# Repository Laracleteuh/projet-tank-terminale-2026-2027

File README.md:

# projet-tank-terminale-2026-2027 ###

Repo GitHub pour le projet de Tank RC des Terminales spécialités sciences de l'ingénieur. Contenu Open Source, et maintenu jusqu'en juillet 2027

### Configuration Requise ###

Ce projet est basé autour de l'Arduino Mega 2560 programmé via VS Code et son extension PlatformIO.
Sur chaque release un fichier .zip a build et un .hex pouvant être uploadé directement sera disponible.
Le fichier d'environnement platformio.ini est publié dans son dossier /PlatformIO/

### Tank OS ###

La dernière version en date de TankOS est TankOS 1.
[Lien vers la dernière release de TankOS](https://github.com/Laracleteuh/projet-tank-terminale-2026-2027/releases/tag/TOS1.1-FU11102026)

*La documentation technique se trouve dans Manuel Utilisateur / Logiciel / TankOS 1.html - .pdf*

### PCB Custom ###

Ce projet contient quelques cartes électroniques faites sur mesure. Les fichiers de celles-ci seront disponibles plus tard dans l'année, quand leur design sera validé et fonctionnel.
Ces designs ont étés fait sur KiCAD.

### Python Scripts ###

Ce projet contient un dossier réservé à des scripts python. Ils sont fait maison et permettent de calculer des caractéristiques en rapport avec les moteurs plus facilement, n'hesitez pas à vous en servir si besoin ;). Pour moins se casser la tête pour des valeurs par défaut, dans la première input, tapez "def" pour charger les valeurs par défaut du programme. Elles seront mises à jour si jamais elles changent au cours du projet.

### MatLab ###

Ce projet contient un dossier réservé aux modèles MatLab et aux calculs. Dans celui-ci vous pourrez trouver le(s) modèle(s) de simulation des moteurs, et la fiche de calcul qui justifie CHAQUE valeur de MatLab (autre que celle qu'on peut trouver dans les docs techniques, vous pouvez chercher quand même, là c'est que les calculs)

### User Manuals ###

Ce projet contient un dossier réservé aux manuels utilisateurs. Ces manuels seront répartis dans des dossiers selon le type d'élément qu'ils présentent (PCB par exemple)

### Feuilles de Calcul ###

Ce projet contient un dossier réservé aux feuilles de calculs pour le tank. Utile si besoin. (Feuilles manuscrites)

---
### Licence ###

Ce projet est distribué sous licence MIT pour le code. Les schémas électroniques et fichiers PCB sont mis à disposition sous licence CERN-OHL-P v2.

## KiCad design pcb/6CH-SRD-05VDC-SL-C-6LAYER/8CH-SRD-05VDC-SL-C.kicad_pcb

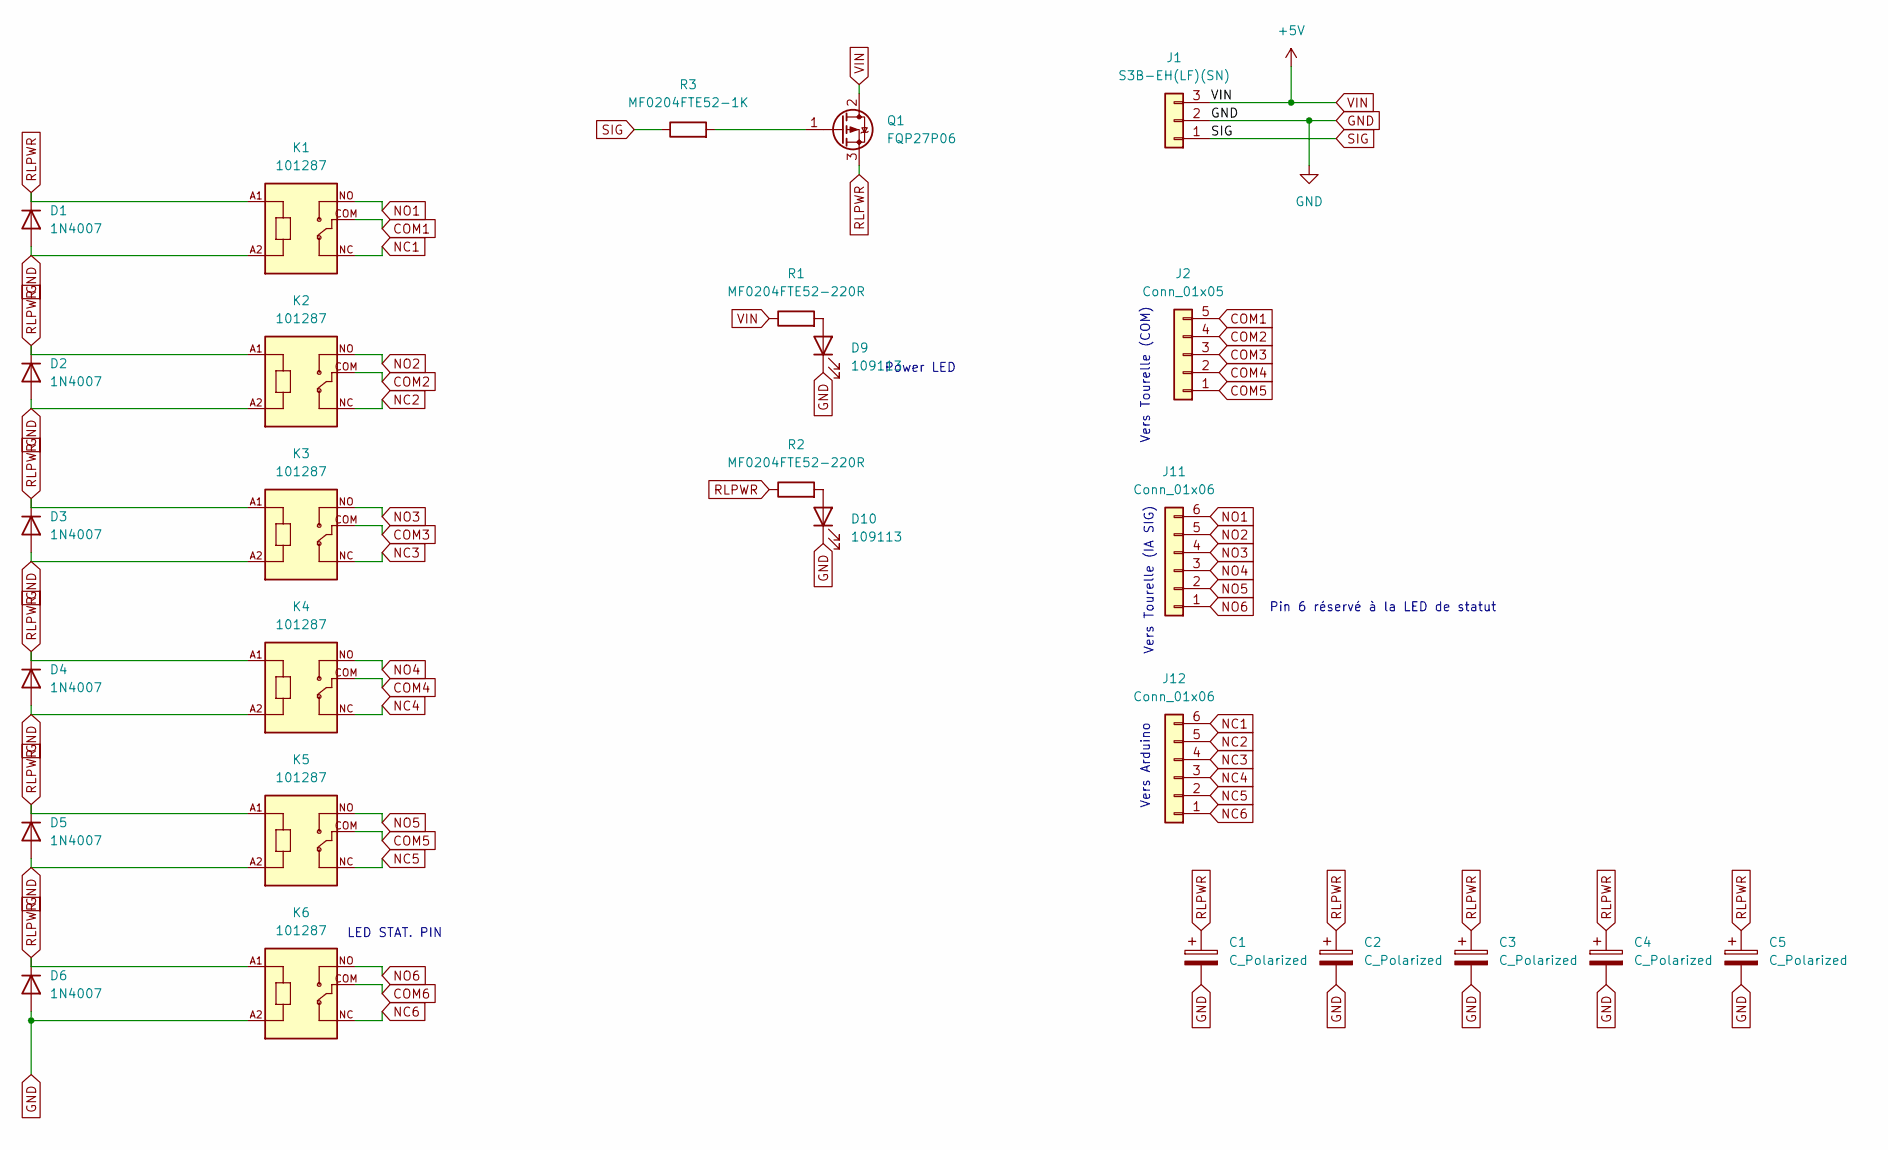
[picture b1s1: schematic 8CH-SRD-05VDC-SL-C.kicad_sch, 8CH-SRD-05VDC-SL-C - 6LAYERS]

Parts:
C1, C2, C3, C4, C5: C_Polarized; CP_Radial_Tantal_D10.5mm_P5.00mm
D1, D2, D3, D4, D5, D6: 1N4007; D_DO-41_SOD81_P10.16mm_Horizontal; Mouser Reference 637-1N4007
D9, D10: 109113; LED_D3.0mm; Mouser Reference 859-LTW-420D7
J1: S3B-EH(LF)(SN); JST_EH_S3B-EH_1x03_P2.50mm_Horizontal; Mouser Reference 306-S3B-EHLFSN
J2: Conn_01x05; JST_EH_S5B-EH_1x05_P2.50mm_Horizontal
J11, J12: Conn_01x06; JST_EH_S6B-EH_1x06_P2.50mm_Horizontal
K1, K2, K3, K4, K5, K6: 101287; RELAY_SRD-05VDC-SL-C; Mouser Reference 392-101287
Q1: FQP27P06; TO-220-3_Horizontal_TabDown
R1, R2: MF0204FTE52-220R; R_Axial_DIN0204_L3.6mm_D1.6mm_P5.08mm_Horizontal; Mouser Reference 603-MF0204FTE52-220R
R3: MF0204FTE52-1K; R_Axial_DIN0204_L3.6mm_D1.6mm_P5.08mm_Horizontal

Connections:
COM1: J2.5, K1.COM
COM2: J2.4, K2.COM
COM3: J2.3, K3.COM
COM4: J2.2, K4.COM
COM5: J2.1, K5.COM
COM6: K6.COM
GND: C1.2, C2.2, C3.2, C4.2, C5.2, D1.2 (A), D2.2 (A), D3.2 (A), D4.2 (A), D5.2 (A), D6.2 (A), D9.1 (K), D10.1 (K), J1.2, K1.A2, K2.A2, K3.A2, K4.A2, K5.A2, K6.A2; also elsewhere on the board
NC1: J12.6, K1.NC
NC2: J12.5, K2.NC
NC3: J12.4, K3.NC
NC4: J12.3, K4.NC
NC5: J12.2, K5.NC
NC6: J12.1, K6.NC
NO1: J11.6, K1.NO
NO2: J11.5, K2.NO
NO3: J11.4, K3.NO
NO4: J11.3, K4.NO
NO5: J11.2, K5.NO
NO6: J11.1, K6.NO; also elsewhere on the board
unnamed: D9.2 (A), R1.2
unnamed: D10.2 (A), R2.2
unnamed: Q1.1 (G), R3.2
RLPWR: C1.1, C2.1, C3.1, C4.1, C5.1, D1.1 (K), D2.1 (K), D3.1 (K), D4.1 (K), D5.1 (K), D6.1 (K), K1.A1, K2.A1, K3.A1, K4.A1, K5.A1, K6.A1, Q1.3 (S), R2.1
SIG: J1.1, R3.1
VIN: J1.3, Q1.2 (D), R1.1

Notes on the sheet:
LED STAT. PIN
Pin 6 réservé à la LED de statut
Vers Tourelle (COM)
Power LED
Vers Tourelle (IA SIG)
Vers Arduino

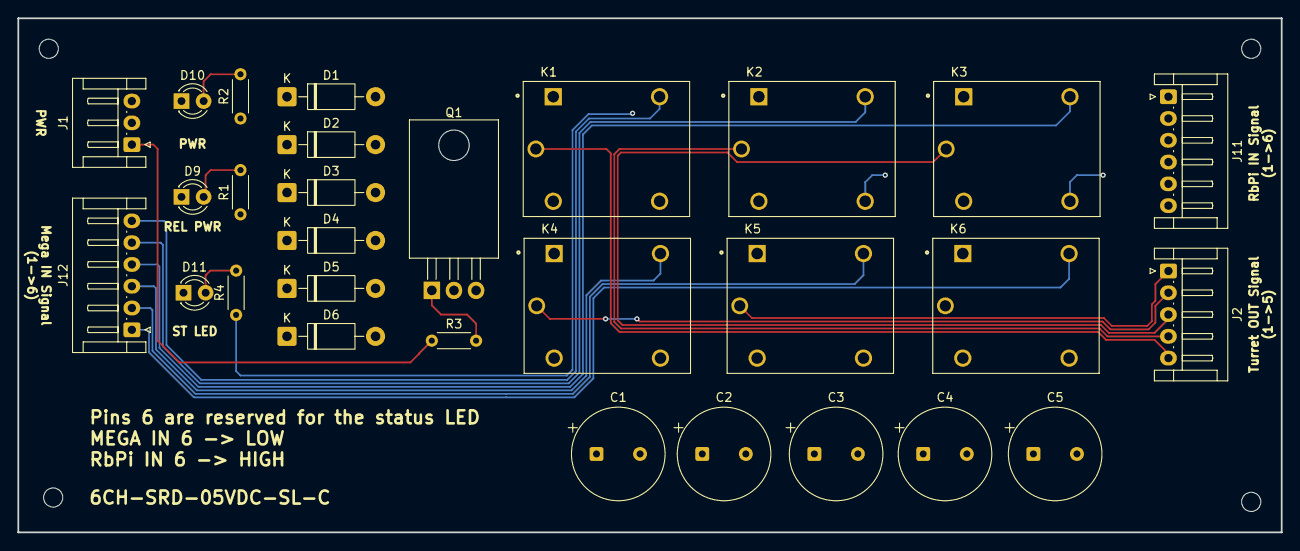
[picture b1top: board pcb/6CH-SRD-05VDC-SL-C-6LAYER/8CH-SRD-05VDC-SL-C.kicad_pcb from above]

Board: 6 copper layers, 145.0 x 59.0 mm, 29 parts (0 on the bottom side), 25 nets.

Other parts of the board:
D11: 109113; LED_D3.0mm
R4: MF0204FTE52-220R; R_Axial_DIN0204_L3.6mm_D1.6mm_P5.08mm_Horizontal

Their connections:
GND: D11.1 (K); also elsewhere on the board
NO6: R4.1; also elsewhere on the board
unnamed: D11.2 (A), R4.2

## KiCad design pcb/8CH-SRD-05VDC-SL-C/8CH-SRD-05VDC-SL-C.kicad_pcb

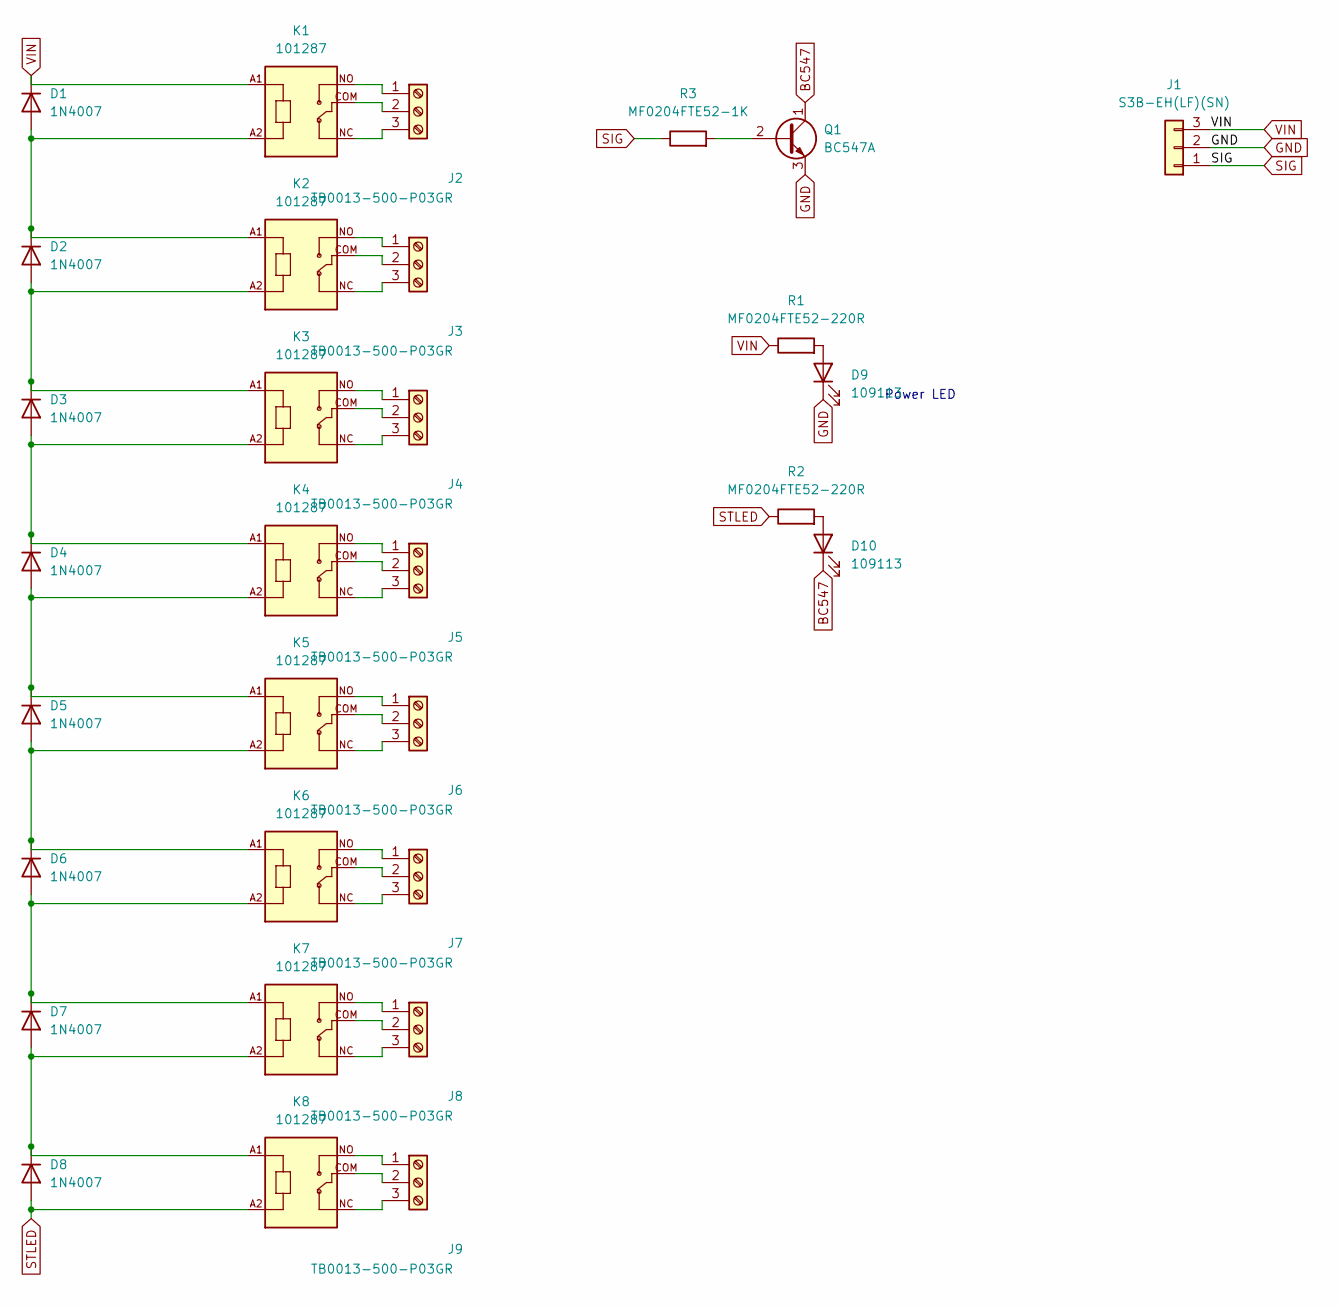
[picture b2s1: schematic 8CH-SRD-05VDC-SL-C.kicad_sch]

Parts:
D1, D2, D3, D4, D5, D6, D7, D8: 1N4007; D_DO-41_SOD81_P10.16mm_Horizontal; Mouser Reference 637-1N4007
D9, D10: 109113; LED_D3.0mm; Mouser Reference 859-LTW-420D7
J1: S3B-EH(LF)(SN); JST_EH_S3B-EH_1x03_P2.50mm_Horizontal; Mouser Reference 306-S3B-EHLFSN
J2, J3, J4, J5, J6, J7, J8, J9: TB0013-500-P03GR; TerminalBlock_MaiXu_MX126-5.0-03P_1x03_P5.00mm; Mouser Reference 179-TB0013-500-P03GR
K1, K2, K3, K4, K5, K6, K7, K8: 101287; RELAY_SRD-05VDC-SL-C; Mouser Reference 392-101287
Q1: BC547A; TO-92_Inline; Mouser Reference 637-BC547A
R1, R2: MF0204FTE52-220R; R_Axial_DIN0204_L3.6mm_D1.6mm_P5.08mm_Horizontal; Mouser Reference 603-MF0204FTE52-220R
R3: MF0204FTE52-1K; R_Axial_DIN0204_L3.6mm_D1.6mm_P5.08mm_Horizontal

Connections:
BC547: D10.1 (K), Q1.1 (C)
GND: D9.1 (K), J1.2, Q1.3 (E)
unnamed: D1.2 (A), D2.1 (K), K1.A2, K2.A1
unnamed: D2.2 (A), D3.1 (K), K2.A2, K3.A1
unnamed: D3.2 (A), D4.1 (K), K3.A2, K4.A1
unnamed: D4.2 (A), D5.1 (K), K4.A2, K5.A1
unnamed: D5.2 (A), D6.1 (K), K5.A2, K6.A1
unnamed: D6.2 (A), D7.1 (K), K6.A2, K7.A1
unnamed: D7.2 (A), D8.1 (K), K7.A2, K8.A1
unnamed: D9.2 (A), R1.2
unnamed: D10.2 (A), R2.2
unnamed: J2.1, K1.NO
unnamed: J2.2, K1.COM
unnamed: J2.3, K1.NC
unnamed: J3.1, K2.NO
unnamed: J3.2, K2.COM
unnamed: J3.3, K2.NC
unnamed: J4.1, K3.NO
unnamed: J4.2, K3.COM
unnamed: J4.3, K3.NC
unnamed: J5.1, K4.NO
unnamed: J5.2, K4.COM
unnamed: J5.3, K4.NC
unnamed: J6.1, K5.NO
unnamed: J6.2, K5.COM
unnamed: J6.3, K5.NC
unnamed: J7.1, K6.NO
unnamed: J7.2, K6.COM
unnamed: J7.3, K6.NC
unnamed: J8.1, K7.NO
unnamed: J8.2, K7.COM
unnamed: J8.3, K7.NC
unnamed: J9.1, K8.NO
unnamed: J9.2, K8.COM
unnamed: J9.3, K8.NC
unnamed: Q1.2 (B), R3.2
SIG: J1.1, R3.1
STLED: D8.2 (A), K8.A2, R2.1
VIN: D1.1 (K), J1.3, K1.A1, R1.1

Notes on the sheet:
Power LED

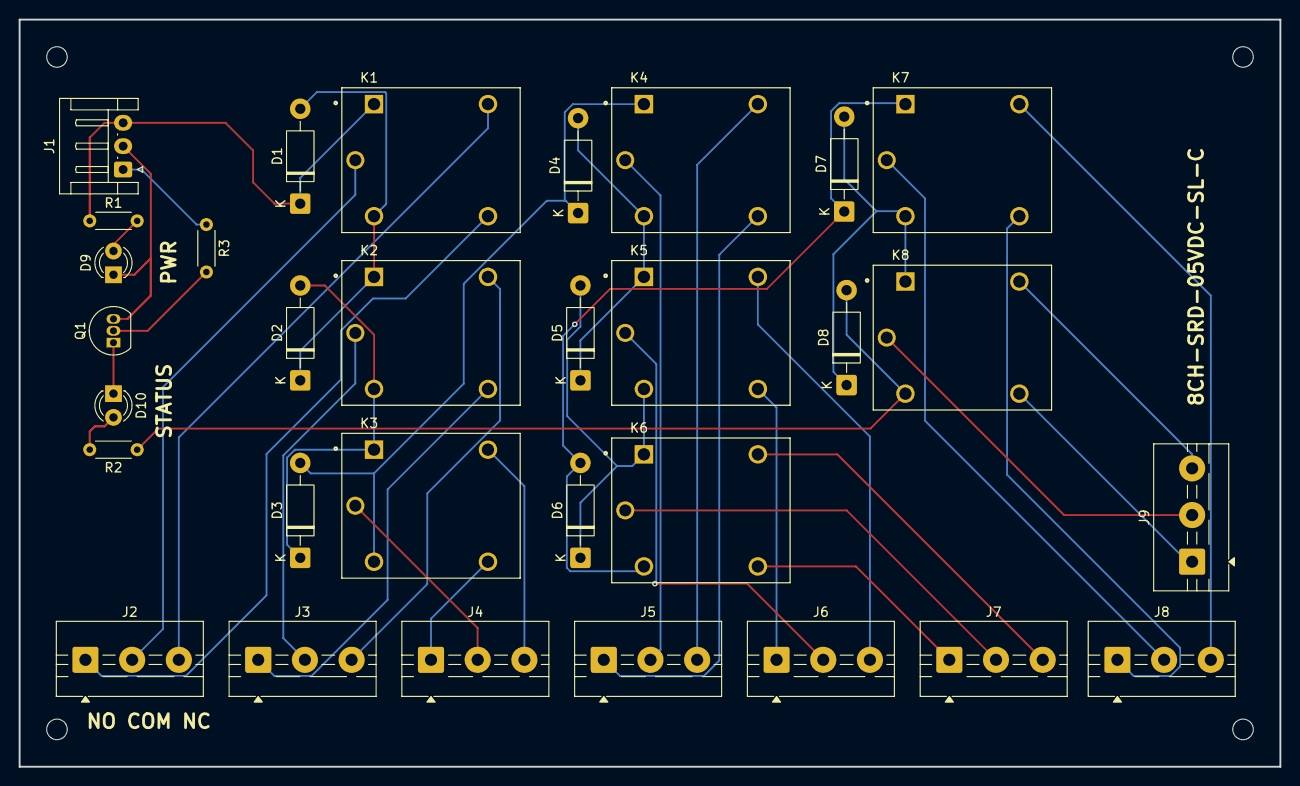
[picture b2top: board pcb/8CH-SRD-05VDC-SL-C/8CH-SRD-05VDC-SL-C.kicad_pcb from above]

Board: 2 copper layers, 135.0 x 80.0 mm, 31 parts (0 on the bottom side), 39 nets.

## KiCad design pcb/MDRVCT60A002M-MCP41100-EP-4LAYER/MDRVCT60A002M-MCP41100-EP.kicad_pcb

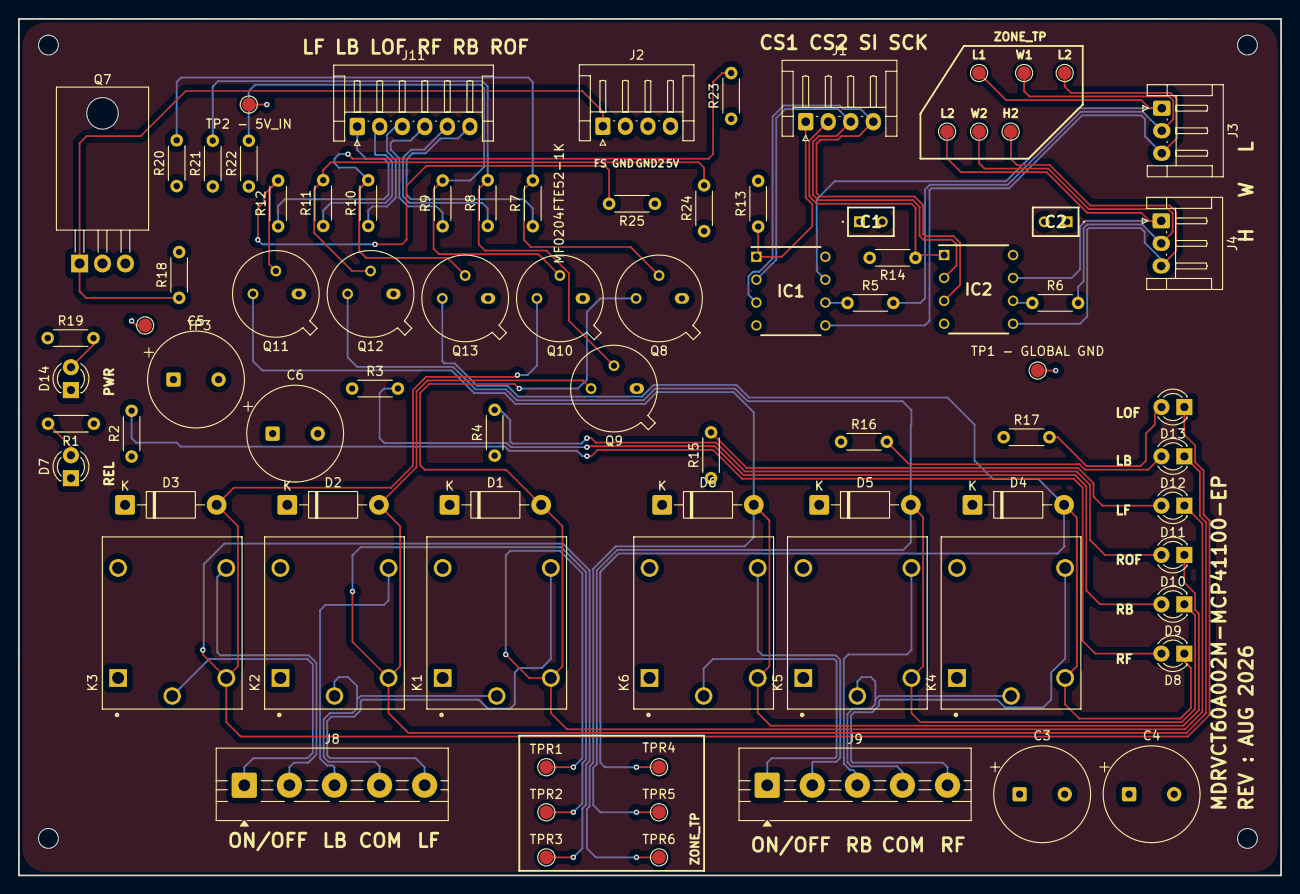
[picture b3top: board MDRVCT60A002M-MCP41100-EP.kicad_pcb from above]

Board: 4 copper layers, 140.0 x 95.0 mm, 86 parts (0 on the bottom side), 52 nets.

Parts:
 : MountingHole_2.2mm_M2
  : MountingHole_2.2mm_M2
 #2,  #3: MountingHole_2.2mm_M2
C1, C2: C320C104M5R5TA7301
C3, C4, C5, C6: C_Polarized; CP_Radial_Tantal_D10.5mm_P5.00mm
D1, D2, D3, D4, D5, D6: 1N4007; D_DO-41_SOD81_P10.16mm_Horizontal
D7, D8, D9, D10, D11, D12, D13, D14: LTW-420D7; LED_D3.0mm_Clear
IC1, IC2: MCP41100-E_P; DIP765W56P254L946H432Q8N
J1, J2: S4B-EH(LF)(SN); JST_EH_S4B-EH_1x04_P2.50mm_Horizontal
J3, J4: S3B-EH(LF)(SN); JST_EH_S3B-EH_1x03_P2.50mm_Horizontal
J8, J9: TB0013-500-P05GR; TerminalBlock_MaiXu_MX126-5.0-05P_1x05_P5.00mm
J11: S6B-EH(LF)(SN); JST_EH_S6B-EH_1x06_P2.50mm_Horizontal
K1, K2, K3, K4, K5, K6: 101287; RELAY_SRD-05VDC-SL-C
Q7: NDP6020P; TO-220-3_Horizontal_TabDown
Q8, Q9, Q10, Q11, Q12, Q13: 2N2219; TO-39-3
R1, R2, R3, R4, R15, R16, R17, R19: MF0204FTE52-220R; R_Axial_DIN0204_L3.6mm_D1.6mm_P5.08mm_Horizontal
R5, R6, R7, R8, R9, R10, R11, R12: MF0204FTE52-1K; R_Axial_DIN0204_L3.6mm_D1.6mm_P5.08mm_Horizontal
R13, R14, R18, R20, R21, R22, R23, R24, R25: MF0204FTE52-10K; R_Axial_DIN0204_L3.6mm_D1.6mm_P5.08mm_Horizontal
TP1 - GLOBAL GND: GND; TestPoint_Pad_D1.5mm
TP2 - 5V_IN: 5V; TestPoint_Pad_D1.5mm
TP3: RELAYS_VCC; TestPoint_Pad_D1.5mm
TP4, TP9: L1; TestPoint_Pad_D1.5mm
TP5: W1; TestPoint_Pad_D1.5mm
TP6: H1; TestPoint_Pad_D1.5mm
TP7: W2; TestPoint_Pad_D1.5mm
TP8: H2; TestPoint_Pad_D1.5mm
TP10: TPR1; TestPoint_Pad_D1.5mm
TP11: TPR2; TestPoint_Pad_D1.5mm
TP12: TPR3; TestPoint_Pad_D1.5mm
TP14: TPR5; TestPoint_Pad_D1.5mm
TP15: TPR6; TestPoint_Pad_D1.5mm
TPR4: TPR4; TestPoint_Pad_D1.5mm

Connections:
CS1: IC1.1 (~CS), J1.1, R13.1
CS2: IC2.1 (~CS), J1.2, R14.1
DRVT1H: IC1.5 (PA0), J3.3, TP6.1 (1_1)
DRVT1L: IC1.7 (PB0), J3.1, TP4.1 (1_1)
DRVT1W: J3.2, R5.2, TP5.1 (1_1)
DRVT2H: IC2.5 (PA0), J4.3, TP8.1 (1_1)
DRVT2L: IC2.7 (PB0), J4.1, TP9.1 (1_1)
DRVT2W: J4.2, R6.2, TP7.1 (1_1)
DRVT3_DIR_BCK_L: J8.3, K2.NO
DRVT3_DIR_COM_L: J8.4, K1.COM, K2.COM
DRVT3_DIR_FWD_L: J8.5, K1.NO
DRVT3_DIR_ONOFF_pin1_L: J8.2, K3.NO
DRVT3_DIR_ONOFF_pin2_L: J8.1, K3.COM
DRVT4_DIR_BCK_R: J9.3, K5.NO
DRVT4_DIR_COM_R: J9.4, K4.COM, K5.COM
DRVT4_DIR_FWD_R: J9.5, K4.NO
DRVT4_DIR_ONOFF_pin1_R: J9.2, K6.NO
DRVT4_DIR_ONOFF_pin2_R: J9.1, K6.COM
FAILSAFE_PIN: J2.1, Q7.1, R18.1
GND: C1.2, C2.2, C3.2, C4.2, C5.2, C6.2, D7.1 (K), D14.1 (K), IC1.4 (VSS), IC2.4 (VSS), J2.2, J2.3, Q8.1 (E), Q9.1 (E), Q10.1 (E), Q11.1 (E), Q12.1 (E), Q13.1 (E), R20.1, R21.1, R22.1, R23.1, R24.1, R25.1, TP1 - GLOBAL GND.1 (1_1)
GNDREL1: D1.2 (A), D11.1 (K), K1.A2, Q8.3 (C), TP10.1 (1_1)
GNDREL2: D2.2 (A), D12.1 (K), K2.A2, Q9.3 (C), TP11.1 (1_1)
GNDREL3: D3.2 (A), D13.1 (K), K3.A2, Q10.3 (C), TP12.1 (1_1)
GNDREL4: D4.2 (A), D8.1 (K), K4.A2, Q13.3 (C), TPR4.1 (1_1)
GNDREL5: D5.2 (A), D9.1 (K), K5.A2, Q12.3 (C), TP14.1 (1_1)
GNDREL6: D6.2 (A), D10.1 (K), K6.A2, Q11.3 (C), TP15.1 (1_1)
unnamed: D7.2 (A), R1.2
unnamed: D8.2 (A), R2.2
unnamed: D9.2 (A), R3.2
unnamed: D10.2 (A), R4.2
unnamed: D11.2 (A), R15.2
unnamed: D12.2 (A), R16.2
unnamed: D13.2 (A), R17.2
unnamed: D14.2 (A), R19.2
unnamed: IC1.6 (PW0), R5.1
unnamed: IC2.6 (PW0), R6.1
unnamed: J11.1, R12.1
unnamed: J11.2, R11.1
unnamed: J11.3, R10.1
unnamed: J11.4, R9.1
unnamed: J11.5, R8.1
unnamed: J11.6, R7.1
RELAYS_VCC: C3.1, C4.1, C5.1, C6.1, D1.1 (K), D2.1 (K), D3.1 (K), D4.1 (K), D5.1 (K), D6.1 (K), K1.A1, K2.A1, K3.A1, K4.A1, K5.A1, K6.A1, Q7.2, R1.1, R2.1, R3.1, R4.1, R15.1, R16.1, R17.1, TP3.1 (1_1)
REL_LMOT_BCK: Q9.2 (B), R8.2, R21.2
REL_LMOT_FWD: Q8.2 (B), R7.2, R20.2
REL_LMOT_ONOFF: Q10.2 (B), R9.2, R22.2
REL_RMOT_BCK: Q12.2 (B), R11.2, R24.2
REL_RMOT_FWD: Q13.2 (B), R10.2, R23.2
REL_RMOT_ONOFF: Q11.2 (B), R12.2, R25.2
SCK: IC1.2 (SCK), IC2.2 (SCK), J1.3
SI: IC1.3 (SI), IC2.3 (SI), J1.4
STAT_LED: C1.1, C2.1, IC1.8 (VDD), IC2.8 (VDD), J2.4, Q7.3, R13.2, R14.2, R18.2, R19.1, TP2 - 5V_IN.1 (1_1)
